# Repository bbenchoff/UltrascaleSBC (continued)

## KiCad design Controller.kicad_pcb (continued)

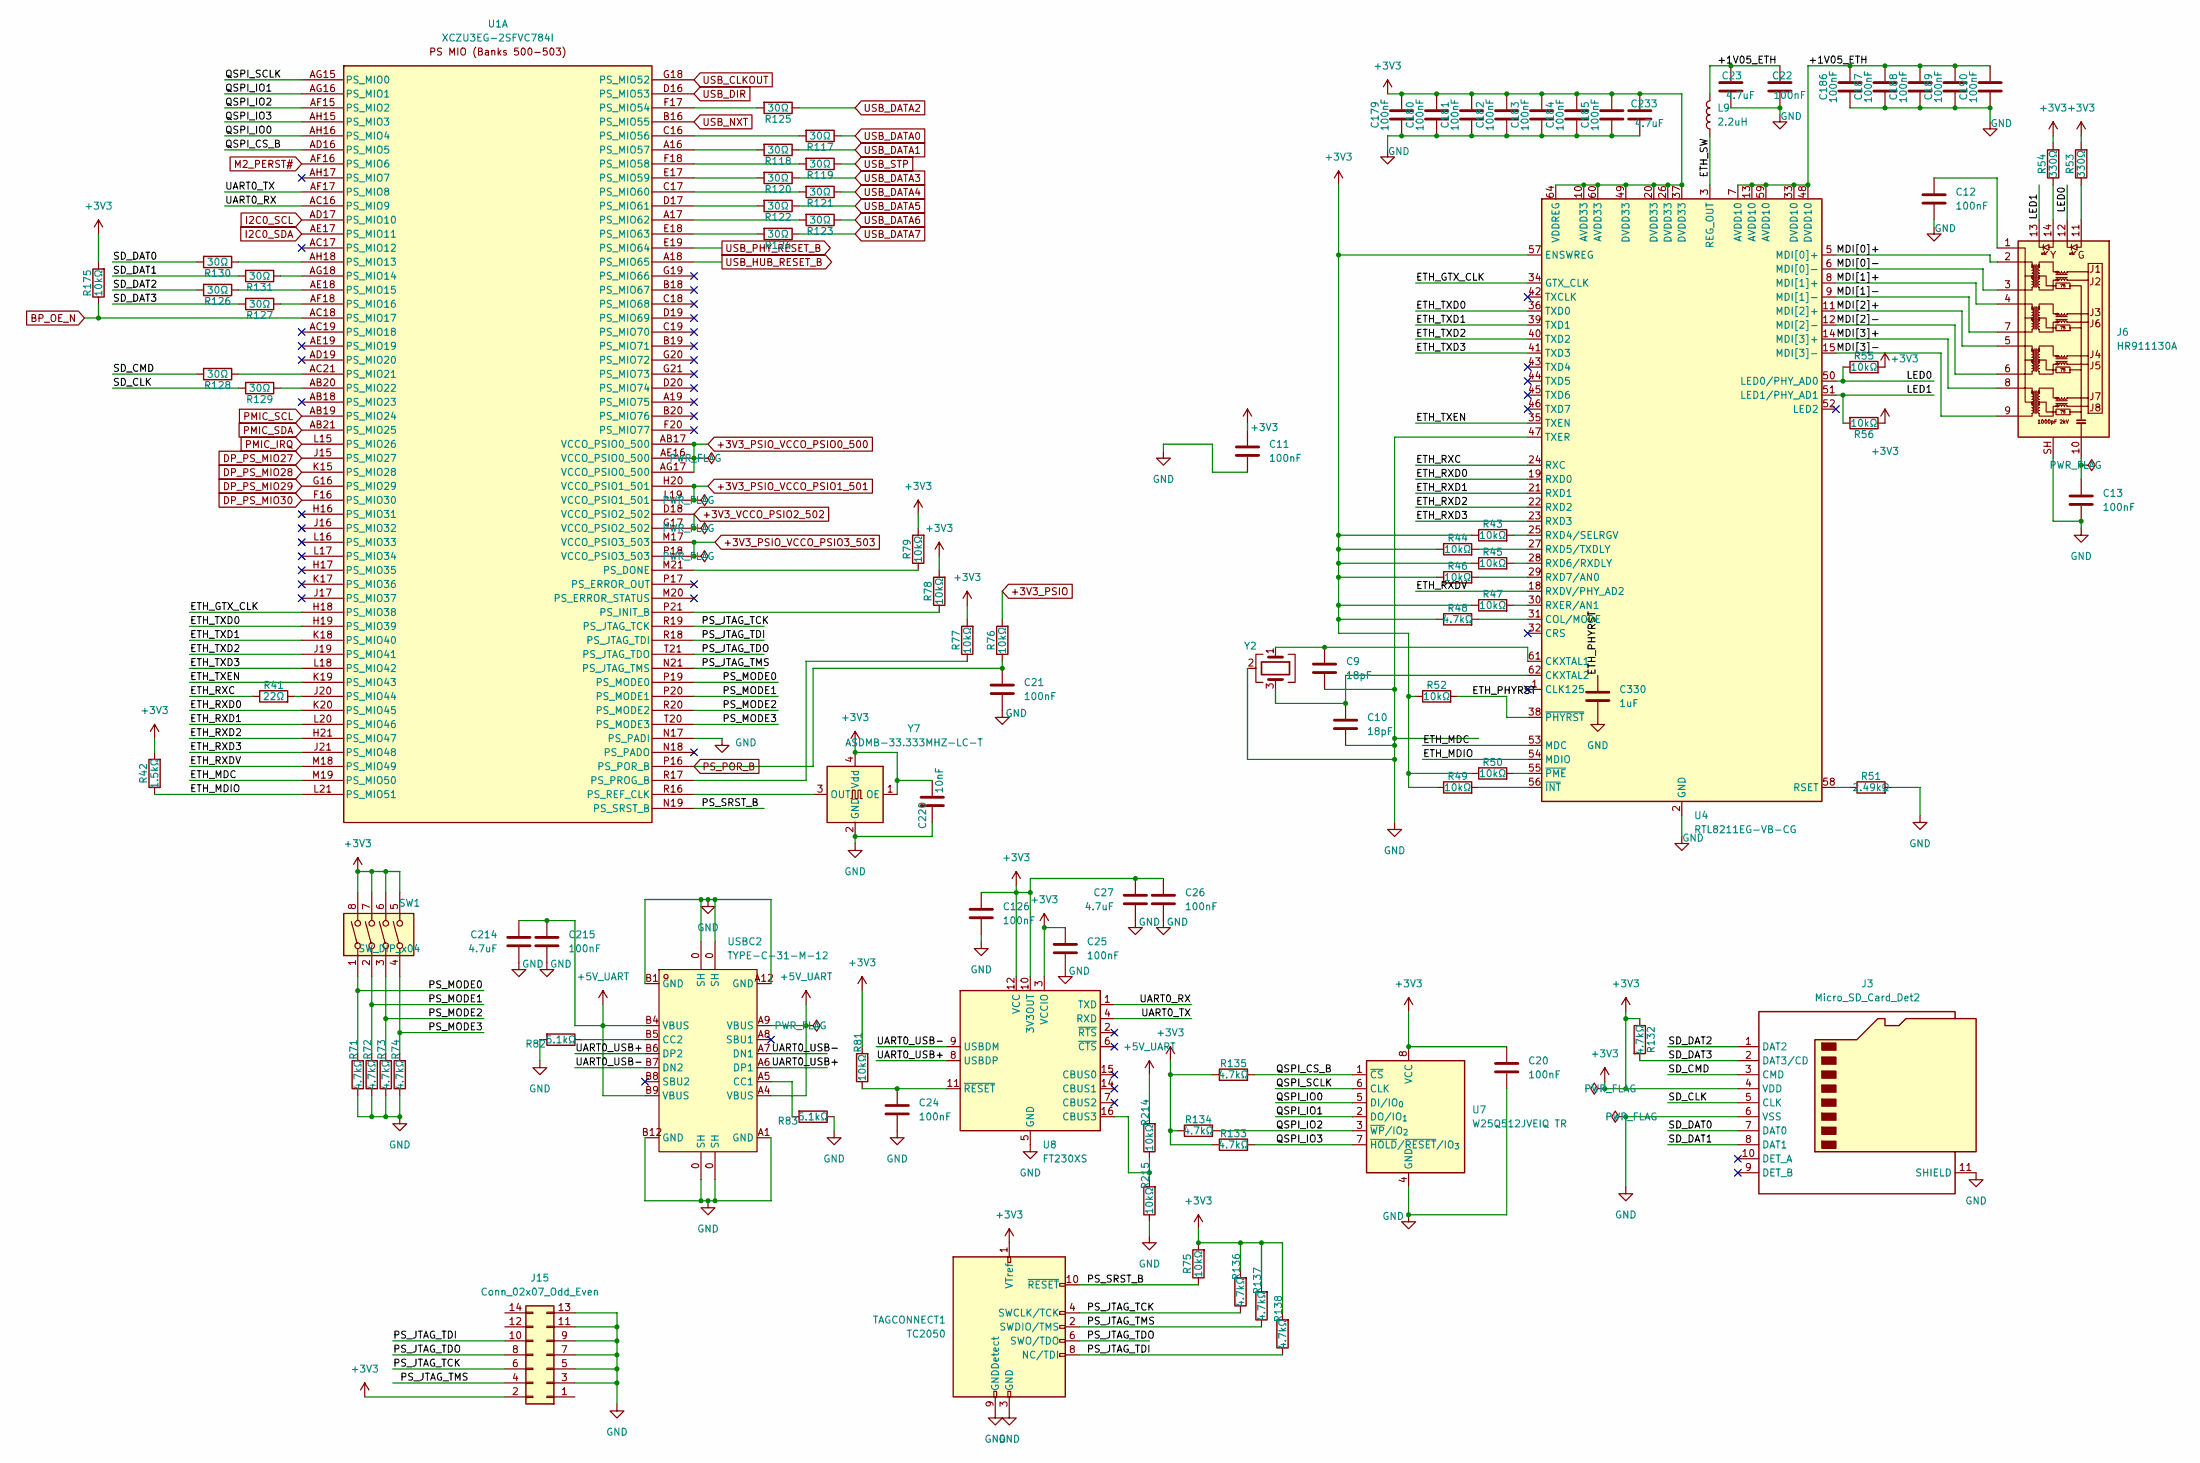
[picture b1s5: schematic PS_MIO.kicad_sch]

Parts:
C9, C10: 18pF; C_0402_1005Metric; MPN 0402CG180J500NT; LCSC C1549
C11, C179, C180, C181, C182, C183, C184, C185, C186, C187, C188, C189, C190: 100nF; C_0402_1005Metric; MPN CL05B104KO5NNNC; LCSC C1525
C12, C13, C20, C21, C22, C24, C25, C26, C126, C215: 100nF; C_1206_3216Metric; MPN CL31B104KBCNNNC; LCSC C24497
C23, C233: 4.7uF; C_0805_2012Metric; MPN CL21A475KPFNNNE; LCSC C96454
C27, C214: 4.7uF; C_1206_3216Metric; MPN 1206B475K500NT; LCSC C29823
C220: 10nF; C_0402_1005Metric; MPN CL05B103KB5NNNC; LCSC C15195
C330: 1uF; C_0402_1005Metric; MPN CL05A105KA5NQNC; LCSC C52923
J3: Micro_SD_Card_Det2; microSD_HC_Hirose_DM3AT-SF-PEJM5; MPN DM3AT-SF-PEJM5; LCSC C114218
J6: HR911130A; RJ45_Hanrun_HR911130A; MPN HR911130A; LCSC C54408
J15: Conn_02x07_Odd_Even; PinHeader_2x07_P2.00mm_Vertical; MPN 878311420; LCSC C240854
L9: 2.2uH; L_Bourns-SRN4018; MPN SRN4018-2R2M; LCSC C913207
R41: 22Ω; R_0402_1005Metric; Tolerance 1%; MPN 0402WGF220JTCE; LCSC C25092
R42: 1.5kΩ; R_0402_1005Metric; Tolerance 1%; MPN 0402WGF1501TCE; LCSC C25867
R43, R44, R45, R46, R47, R49, R50, R52, R55, R56, R75, R76, R77, R78, R79, R81, R175, R214, R215: 10kΩ; R_0402_1005Metric; Tolerance 1%; MPN 0402WGF1002TCE; LCSC C25744
R48, R71, R72, R73, R74, R132, R133, R134, R135, R136, R137, R138: 4.7kΩ; R_0402_1005Metric; Tolerance 1%; MPN 0402WGF4701TCE; LCSC C25900
R51: 2.49kΩ; R_0402_1005Metric; Tolerance 1%; MPN 0402WGF2491TCE; LCSC C25884
R53, R54: 330Ω; R_0402_1005Metric; Tolerance 1%; MPN 0402WGF3300TCE; LCSC C25104
R82, R83: 5.1kΩ; R_0402_1005Metric; Tolerance 1%; MPN 0402WGF5101TCE; LCSC C25905
R117, R118, R119, R120, R121, R122, R123, R124, R125, R126, R127, R128, R129, R130, R131: 30Ω; R_0402_1005Metric; Tolerance 1%; MPN RC0402FR-0730RL; LCSC C138007
SW1: SW_DIP_x04; SW_DIP_SPSTx04_Slide_6.7x11.72mm_W7.62mm_P2.54mm_LowProfile; MPN DSWB04LHGET; LCSC C99418
TAGCONNECT1: TC2050; Tag-Connect_TC2050-IDC-FP_2x05_P1.27mm_Vertical
U1: XCZU3EG-2SFVC784I; SFVC784_AMD; MPN XCZU3EG-2SFVC784I; LCSC C1550463
U4: RTL8211EG-VB-CG; QFN-64-1EP_9x9mm_P0.5mm_EP3.8x3.8mm; MPN RTL8211EG-VB-CG; LCSC C69264
U7: W25Q512JVEIQ TR; WSON-8-1EP_8x6mm_P1.27mm_EP3.4x4.3mm; MPN W25Q512JVEIQ; LCSC C7389628
U8: FT230XS; SSOP-16_3.9x4.9mm_P0.635mm; MPN FT230XS-R; LCSC C69082
USBC2: TYPE-C-31-M-12; USB-C_SMD-TYPE-C-31-M-12; MPN TYPE-C-31-M-12; LCSC Part C165948
Y2: Crystal_GND24; Crystal_SMD_3225-4Pin_3.2x2.5mm; Part Number X322525MOB4SI; LCSC C20617567
Y7: ASDMB-33.333MHZ-LC-T; ASDMB_2520; MPN ASDMB-33.333MHZ-LC-T; LCSC C17497075

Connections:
+3V3: C11.1, C20.1, C25.1, C26.1, C27.1, C126.1, C179.2, C180.2, C181.2, C182.2, C183.2, C184.2, C185.2, C220.2, C233.1, J3.4 (VDD), J15.2, R42.2, R43.1, R44.1, R45.1, R46.1, R47.1, R48.1, R49.1, R50.1, R52.1, R53.2, R54.2, R55.2, R56.1, R75.2, R77.2, R78.2, R79.2, R81.2, R132.1, R133.1, R134.1, R135.1, R136.2, R137.2, R138.2, R175.2, SW1.5, SW1.6, SW1.7, SW1.8, TAGCONNECT1.1 (VTref), U4.10 (AVDD33), U4.20 (DVDD33), U4.26 (DVDD33), U4.37 (DVDD33), U4.49 (DVDD33), U4.57 (ENSWREG), U4.60 (AVDD33), U4.64 (VDDREG), U7.8 (VCC), U8.3 (VCCIO), U8.10 (3V3OUT), U8.12 (VCC), Y7.1 (OE), Y7.4 (Vdd); also elsewhere on the board
+3V3_PSIO: R76.2, U1.AB17 (VCCO_PSIO0_500), U1.AE16 (VCCO_PSIO0_500), U1.AG17 (VCCO_PSIO0_500), U1.D18 (VCCO_PSIO2_502), U1.G17 (VCCO_PSIO2_502), U1.H20 (VCCO_PSIO1_501), U1.L19 (VCCO_PSIO1_501), U1.M17 (VCCO_PSIO3_503), U1.P18 (VCCO_PSIO3_503); also elsewhere on the board
+5V_UART: C214.1, C215.1, R214.2, USBC2.A4 (VBUS), USBC2.A9 (VBUS), USBC2.B4 (VBUS), USBC2.B9 (VBUS)
/PS_MIO/+1V05_ETH: C22.1, C23.1, C186.2, C187.2, C188.2, C189.2, C190.2, L9.2, U4.7 (AVDD10), U4.13 (AVDD10), U4.33 (DVDD10), U4.48 (DVDD10), U4.59 (AVDD10)
/PS_MIO/ETH_GTX_CLK: U1.H18 (PS_MIO38), U4.34 (GTX_CLK)
/PS_MIO/ETH_MDC: U1.M19 (PS_MIO50), U4.53 (MDC)
/PS_MIO/ETH_MDIO: R42.1, U1.L21 (PS_MIO51), U4.54 (MDIO)
/PS_MIO/ETH_PHYRST: C330.1, R52.2, U4.38 (~PHYRST)
/PS_MIO/ETH_RXC: R41.1, U4.24 (RXC)
/PS_MIO/ETH_RXD0: U1.K20 (PS_MIO45), U4.19 (RXD0)
/PS_MIO/ETH_RXD1: U1.L20 (PS_MIO46), U4.21 (RXD1)
/PS_MIO/ETH_RXD2: U1.H21 (PS_MIO47), U4.22 (RXD2)
/PS_MIO/ETH_RXD3: U1.J21 (PS_MIO48), U4.23 (RXD3)
/PS_MIO/ETH_RXDV: U1.M18 (PS_MIO49), U4.18 (RXDV/PHY_AD2)
/PS_MIO/ETH_SW: L9.1, U4.3 (REG_OUT)
/PS_MIO/ETH_TXD0: U1.H19 (PS_MIO39), U4.36 (TXD0)
/PS_MIO/ETH_TXD1: U1.K18 (PS_MIO40), U4.39 (TXD1)
/PS_MIO/ETH_TXD2: U1.J19 (PS_MIO41), U4.40 (TXD2)
/PS_MIO/ETH_TXD3: U1.L18 (PS_MIO42), U4.41 (TXD3)
/PS_MIO/ETH_TXEN: U1.K19 (PS_MIO43), U4.35 (TXEN)
/PS_MIO/LED0: J6.12, R55.1, U4.50 (LED0/PHY_AD0)
/PS_MIO/LED1: J6.13, R56.2, U4.51 (LED1/PHY_AD1)
/PS_MIO/MDI[0]+: J6.2 (TD1+), U4.5 (MDI[0]+)
/PS_MIO/MDI[0]-: J6.3 (TD1-), U4.6 (MDI[0]-)
/PS_MIO/MDI[1]+: J6.4 (TD2+), U4.8 (MDI[1]+)
/PS_MIO/MDI[1]-: J6.7 (TD2-), U4.9 (MDI[1]-)
/PS_MIO/MDI[2]+: J6.5 (TD3+), U4.11 (MDI[2]+)
/PS_MIO/MDI[2]-: J6.6 (TD3-), U4.12 (MDI[2]-)
/PS_MIO/MDI[3]+: J6.8 (TD4+), U4.14 (MDI[3]+)
/PS_MIO/MDI[3]-: J6.9 (TD4-), U4.15 (MDI[3]-)
/PS_MIO/PS_JTAG_TCK: J15.6, R136.1, TAGCONNECT1.4 (SWCLK/TCK), U1.R19 (PS_JTAG_TCK)
/PS_MIO/PS_JTAG_TDI: J15.10, R138.1, TAGCONNECT1.8 (NC/TDI), U1.R18 (PS_JTAG_TDI)
/PS_MIO/PS_JTAG_TDO: J15.8, TAGCONNECT1.6 (SWO/TDO), U1.T21 (PS_JTAG_TDO)
/PS_MIO/PS_JTAG_TMS: J15.4, R137.1, TAGCONNECT1.2 (SWDIO/TMS), U1.N21 (PS_JTAG_TMS)
/PS_MIO/PS_MODE0: R71.2, SW1.1, U1.P19 (PS_MODE0)
/PS_MIO/PS_MODE1: R72.2, SW1.2, U1.P20 (PS_MODE1)
/PS_MIO/PS_MODE2: R73.2, SW1.3, U1.R20 (PS_MODE2)
/PS_MIO/PS_MODE3: R74.2, SW1.4, U1.T20 (PS_MODE3)
/PS_MIO/PS_SRST_B: R75.1, TAGCONNECT1.10 (~RESET), U1.N19 (PS_SRST_B); also elsewhere on the board
/PS_MIO/QSPI_CS_B: R135.2, U1.AD16 (PS_MIO5), U7.1 (~CS)
/PS_MIO/QSPI_IO0: U1.AH16 (PS_MIO4), U7.5 (DI/IO_{0})
/PS_MIO/QSPI_IO1: U1.AG16 (PS_MIO1), U7.2 (DO/IO_{1})
/PS_MIO/QSPI_IO2: R134.2, U1.AF15 (PS_MIO2), U7.3 (~WP/IO_{2})
/PS_MIO/QSPI_IO3: R133.2, U1.AH15 (PS_MIO3), U7.7 (~HOLD/~RESET/IO_{3})
/PS_MIO/QSPI_SCLK: U1.AG15 (PS_MIO0), U7.6 (CLK)
/PS_MIO/SD_CLK: J3.5 (CLK), R129.2
/PS_MIO/SD_CMD: J3.3 (CMD), R128.2
/PS_MIO/SD_DAT0: J3.7 (DAT0), R130.2
/PS_MIO/SD_DAT1: J3.8 (DAT1), R131.2
/PS_MIO/SD_DAT2: J3.1 (DAT2), R126.2
/PS_MIO/SD_DAT3: J3.2 (DAT3/CD), R127.2, R132.2
/PS_MIO/UART0_RX: U1.AC16 (PS_MIO9), U8.1 (TXD)
/PS_MIO/UART0_TX: U1.AF17 (PS_MIO8), U8.4 (RXD)
/PS_MIO/UART0_USB+: U8.8 (USBDP), USBC2.A6 (DP1), USBC2.B6 (DP2)
/PS_MIO/UART0_USB-: U8.9 (USBDM), USBC2.A7 (DN1), USBC2.B7 (DN2)
BP_OE_N: R175.1, U1.AC18 (PS_MIO17); also elsewhere on the board
DP_HPD: U1.K15 (PS_MIO28); also elsewhere on the board
DP_PS_MIO27: U1.J15 (PS_MIO27); also elsewhere on the board
DP_PS_MIO29: U1.G16 (PS_MIO29); also elsewhere on the board
DP_PS_MIO30: U1.F16 (PS_MIO30); also elsewhere on the board
GND: C9.2, C10.2, C11.2, C12.2, C13.2, C20.2, C21.2, C22.2, C23.2, C24.2, C25.2, C26.2, C27.2, C126.2, C179.1, C180.1, C181.1, C182.1, C183.1, C184.1, C185.1, C186.1, C187.1, C188.1, C189.1, C190.1, C214.2, C215.2, C220.1, C233.2, C330.2, J3.6 (VSS), J3.11 (SHIELD), J6.SH, J15.3, J15.5, J15.7, J15.9, J15.11, J15.13, R51.2, R71.1, R72.1, R73.1, R74.1, R82.2, R83.1, R215.1, TAGCONNECT1.3 (GND), TAGCONNECT1.5 (GND), TAGCONNECT1.9 (GNDDetect), U1.N17 (PS_PADI), U4.2 (GND), U4.4 (GND), U4.47 (TXER), U4.63 (GND), U4.65 (GND), U7.4 (GND), U8.5 (GND), U8.13 (GND), USBC2.0 (SH), USBC2.A1 (GND), USBC2.A12 (GND), USBC2.B1 (GND), USBC2.B12 (GND), Y2.2 (G), Y2.4 (G), Y7.2 (GND); also elsewhere on the board
I2C0_SCL: U1.AD17 (PS_MIO10); also elsewhere on the board
I2C0_SDA: U1.AE17 (PS_MIO11); also elsewhere on the board
M2_PERST#: U1.AF16 (PS_MIO6); also elsewhere on the board
unnamed: C12.1, J6.1 (CT)
unnamed: C13.1, J6.10 (GND)
unnamed: J6.11, R53.1
unnamed: J6.14, R54.1
unnamed: R79.1, U1.M21 (PS_DONE)
unnamed: R78.1, U1.P21 (PS_INIT_B)
unnamed: R130.1, U1.AH18 (PS_MIO13)
unnamed: R131.1, U1.AG18 (PS_MIO14)
unnamed: R126.1, U1.AE18 (PS_MIO15)
unnamed: R127.1, U1.AF18 (PS_MIO16)
unnamed: R128.1, U1.AC21 (PS_MIO21)
unnamed: R129.1, U1.AB20 (PS_MIO22)
unnamed: R41.2, U1.J20 (PS_MIO44)
unnamed: R125.2, U1.F17 (PS_MIO54)
unnamed: R117.2, U1.C16 (PS_MIO56)
unnamed: R118.2, U1.A16 (PS_MIO57)
unnamed: R119.2, U1.F18 (PS_MIO58)
unnamed: R120.2, U1.E17 (PS_MIO59)
unnamed: R121.2, U1.C17 (PS_MIO60)
unnamed: R122.2, U1.D17 (PS_MIO61)
unnamed: R123.2, U1.A17 (PS_MIO62)
unnamed: R124.2, U1.E18 (PS_MIO63)
unnamed: R77.1, U1.R17 (PS_PROG_B)
unnamed: U1.R16 (PS_REF_CLK), Y7.3 (OUT)
unnamed: C9.1, U4.61 (CKXTAL1), Y2.1
unnamed: C10.1, U4.62 (CKXTAL2), Y2.3
unnamed: R48.2, U4.31 (COL/MODE)
unnamed: R51.1, U4.58 (RSET)
unnamed: R43.2, U4.25 (RXD4/SELRGV)
unnamed: R44.2, U4.27 (RXD5/TXDLY)
unnamed: R45.2, U4.28 (RXD6/RXDLY)
unnamed: R46.2, U4.29 (RXD7/AN0)
unnamed: R47.2, U4.30 (RXER/AN1)
unnamed: R49.2, U4.56 (~INT)
unnamed: R50.2, U4.55 (~PME)
unnamed: R214.1, R215.2, U8.16 (CBUS3)
unnamed: C24.1, R81.1, U8.11 (~RESET)
unnamed: R83.2, USBC2.A5 (CC1)
unnamed: R82.1, USBC2.B5 (CC2)
PMIC_IRQ: U1.L15 (PS_MIO26); also elsewhere on the board
PMIC_SCL: U1.AB19 (PS_MIO24); also elsewhere on the board
PMIC_SDA: U1.AB21 (PS_MIO25); also elsewhere on the board
PS_POR_B: C21.1, R76.1, U1.P16 (PS_POR_B); also elsewhere on the board
USB_CLKOUT: U1.G18 (PS_MIO52); also elsewhere on the board
USB_DATA0: R117.1; also elsewhere on the board
USB_DATA1: R118.1; also elsewhere on the board
USB_DATA2: R125.1; also elsewhere on the board
USB_DATA3: R120.1; also elsewhere on the board
USB_DATA4: R121.1; also elsewhere on the board
USB_DATA5: R122.1; also elsewhere on the board
USB_DATA6: R123.1; also elsewhere on the board
USB_DATA7: R124.1; also elsewhere on the board
USB_DIR: U1.D16 (PS_MIO53); also elsewhere on the board
USB_HUB_RESET_B: U1.A18 (PS_MIO65); also elsewhere on the board
USB_NXT: U1.B16 (PS_MIO55); also elsewhere on the board
USB_PHY_RESET_B: U1.E19 (PS_MIO64); also elsewhere on the board
USB_STP: R119.1; also elsewhere on the board

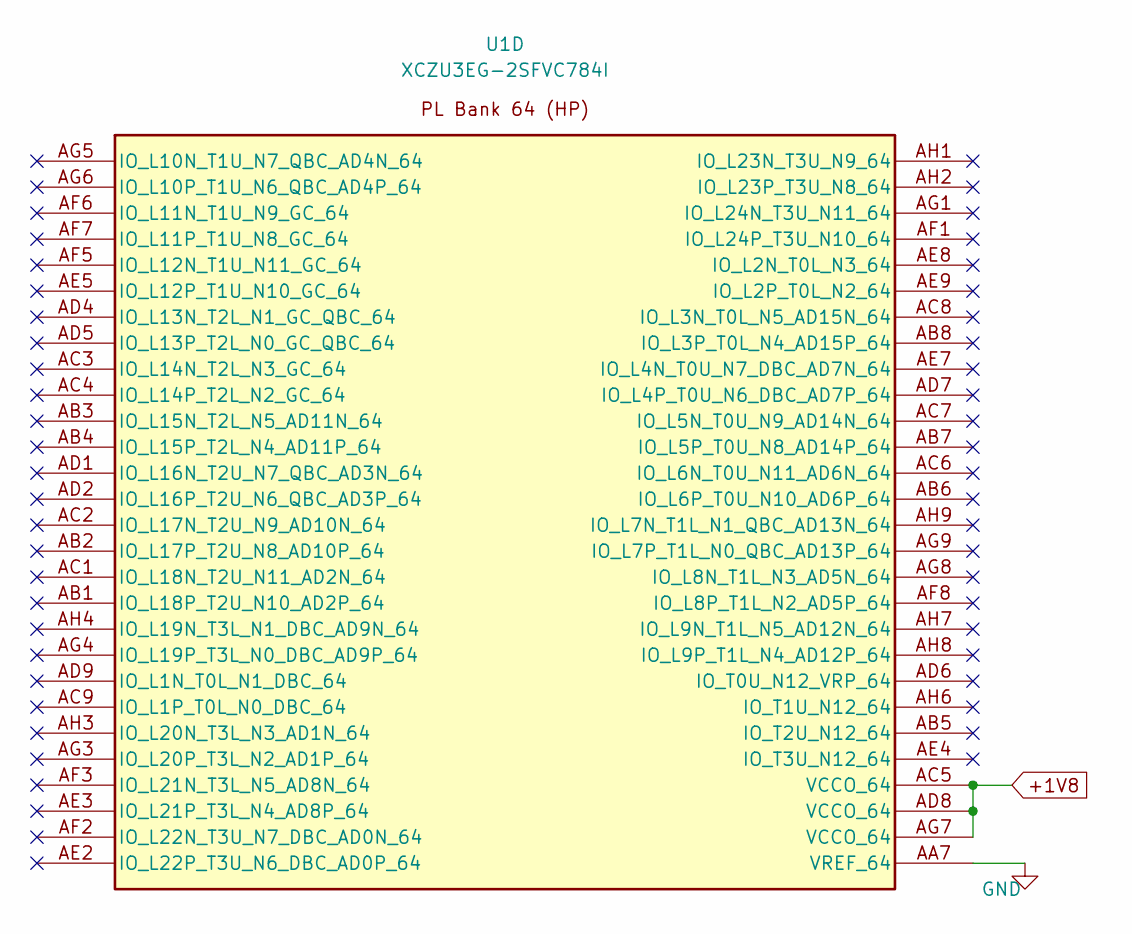
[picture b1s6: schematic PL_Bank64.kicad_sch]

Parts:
U1: XCZU3EG-2SFVC784I; SFVC784_AMD; MPN XCZU3EG-2SFVC784I; LCSC C1550463

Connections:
+1V8: U1.AC5 (VCCO_64), U1.AD8 (VCCO_64), U1.AG7 (VCCO_64); also elsewhere on the board
GND: U1.AA7 (VREF_64); also elsewhere on the board

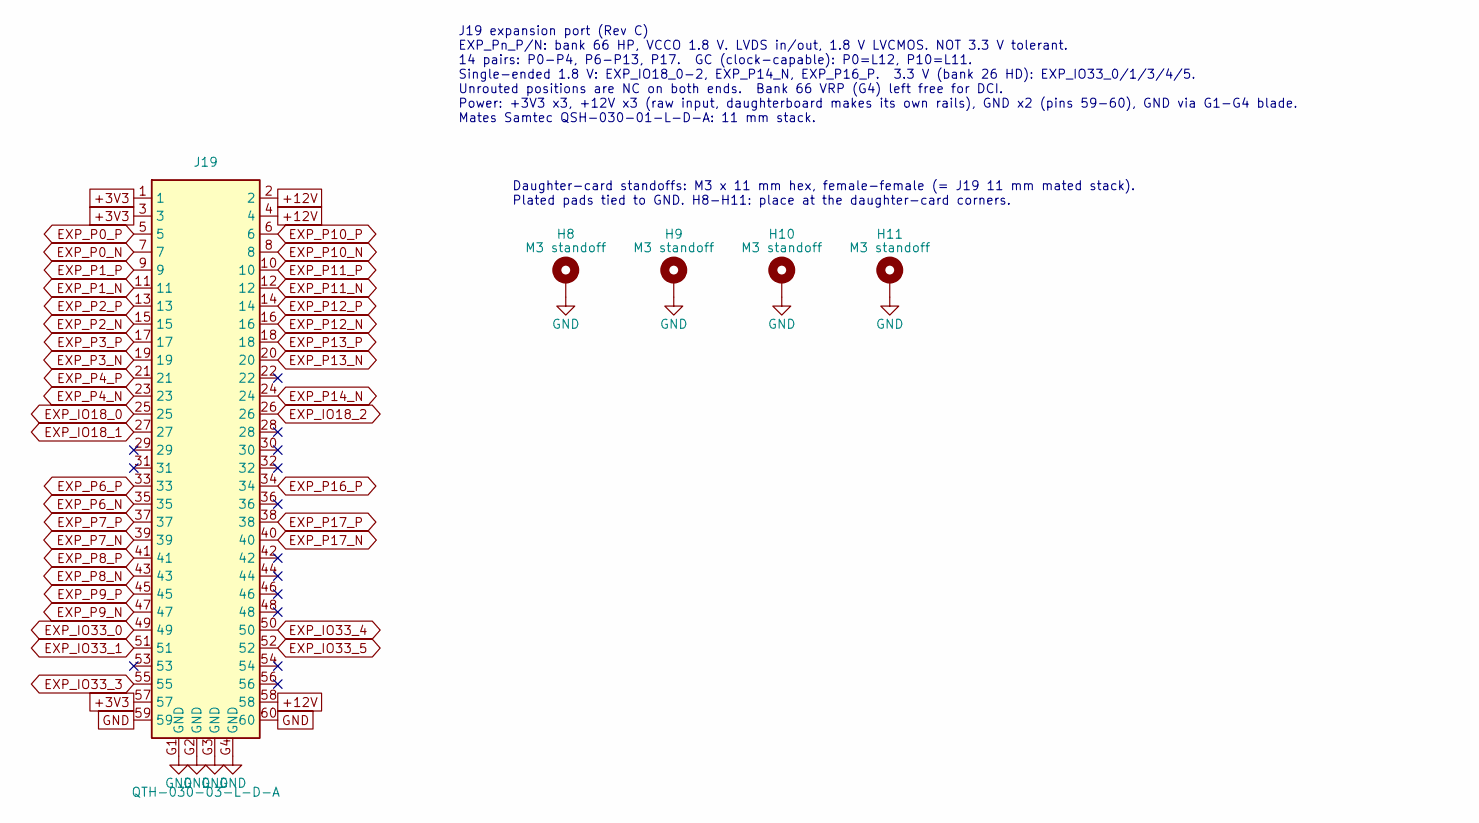
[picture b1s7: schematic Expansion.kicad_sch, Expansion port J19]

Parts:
H8, H9, H10, H11: M3 standoff; MountingHole_3.2mm_M3_Pad_Via
J19: QTH-030-03-L-D-A; Samtec_QTH-030-03-L-D-A; MPN QTH-030-03-L-D-A; LCSC C5296114

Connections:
+3V3: J19.1, J19.3, J19.57; also elsewhere on the board
+12V: J19.2, J19.4, J19.58; also elsewhere on the board
EXP_IO18_0: J19.25; also elsewhere on the board
EXP_IO18_1: J19.27; also elsewhere on the board
EXP_IO18_2: J19.26; also elsewhere on the board
EXP_IO33_0: J19.49; also elsewhere on the board
EXP_IO33_1: J19.51; also elsewhere on the board
EXP_IO33_3: J19.55; also elsewhere on the board
EXP_IO33_4: J19.50; also elsewhere on the board
EXP_IO33_5: J19.52; also elsewhere on the board
EXP_P0_N: J19.7; also elsewhere on the board
EXP_P0_P: J19.5; also elsewhere on the board
EXP_P1_N: J19.11; also elsewhere on the board
EXP_P1_P: J19.9; also elsewhere on the board
EXP_P2_N: J19.15; also elsewhere on the board
EXP_P2_P: J19.13; also elsewhere on the board
EXP_P3_N: J19.19; also elsewhere on the board
EXP_P3_P: J19.17; also elsewhere on the board
EXP_P4_N: J19.23; also elsewhere on the board
EXP_P4_P: J19.21; also elsewhere on the board
EXP_P6_N: J19.35; also elsewhere on the board
EXP_P6_P: J19.33; also elsewhere on the board
EXP_P7_N: J19.39; also elsewhere on the board
EXP_P7_P: J19.37; also elsewhere on the board
EXP_P8_N: J19.43; also elsewhere on the board
EXP_P8_P: J19.41; also elsewhere on the board
EXP_P9_N: J19.47; also elsewhere on the board
EXP_P9_P: J19.45; also elsewhere on the board
EXP_P10_N: J19.8; also elsewhere on the board
EXP_P10_P: J19.6; also elsewhere on the board
EXP_P11_N: J19.12; also elsewhere on the board
EXP_P11_P: J19.10; also elsewhere on the board
EXP_P12_N: J19.16; also elsewhere on the board
EXP_P12_P: J19.14; also elsewhere on the board
EXP_P13_N: J19.20; also elsewhere on the board
EXP_P13_P: J19.18; also elsewhere on the board
EXP_P14_N: J19.24; also elsewhere on the board
EXP_P16_P: J19.34; also elsewhere on the board
EXP_P17_N: J19.40; also elsewhere on the board
EXP_P17_P: J19.38; also elsewhere on the board
GND: H8.1 (1_1), H9.1 (1_1), H10.1 (1_1), H11.1 (1_1), J19.59, J19.60, J19.G1 (GND), J19.G2 (GND), J19.G3 (GND), J19.G4 (GND); also elsewhere on the board

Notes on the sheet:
J19 expansion port (Rev C) EXP_Pn_P/N: bank 66 HP, VCCO 1.8 V. LVDS in/out, 1.8 V LVCMOS. NOT 3.3 V tolerant. 14 pairs: P0-P4, P6-P13, P17. GC (clock-capable): P0=L12, P10=L11. Single-ended 1.8 V: EXP_IO18_0-2, EXP_P14_N, EXP_P16_P. 3.3 V (bank 26 HD): EXP_IO33_0/1/3/4/5. Unrouted positions are NC 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
Daughter-card standoffs: M3 x 11 mm hex, female-female (= J19 11 mm mated stack). Plated pads tied to GND. H8-H11: place at the daughter-card corners.

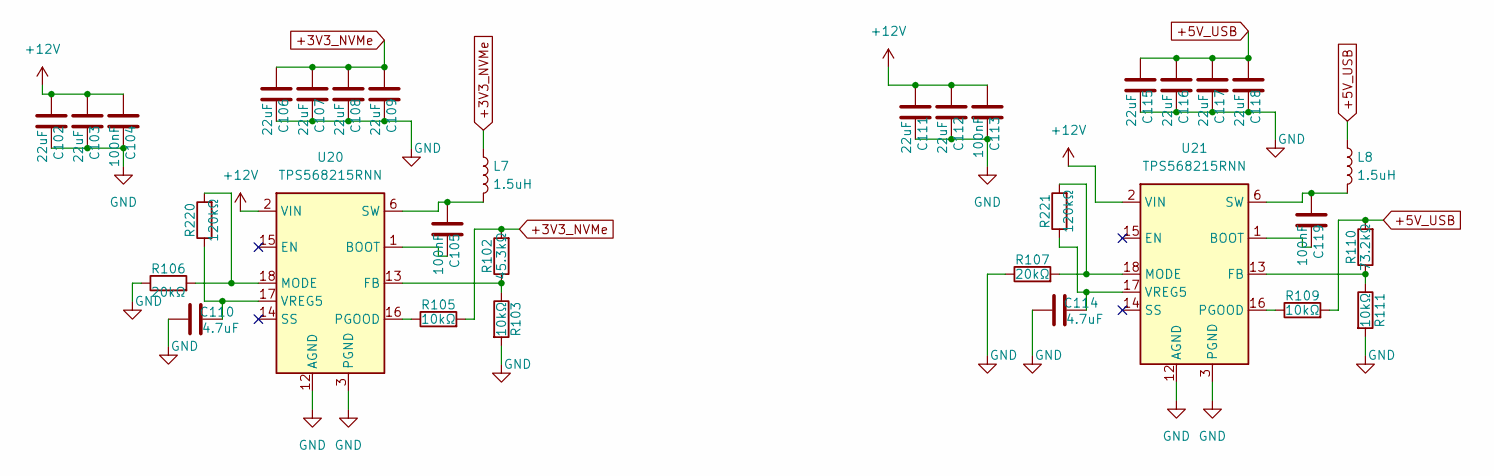
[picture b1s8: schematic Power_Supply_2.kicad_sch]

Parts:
C102, C103, C111, C112: 22uF; C_0805_2012Metric; MPN CGA0805X5R226M250MT; LCSC C6119899
C104, C105, C113, C119: 100nF; C_0402_1005Metric; MPN CL05B104KO5NNNC; LCSC C1525
C106, C107, C108, C109, C115, C116, C117, C118: 22uF; C_0603_1608Metric; MPN CC0603MRX5R5BB226; LCSC C109448
C110, C114: 4.7uF; C_0805_2012Metric; MPN CL21A475KAQNNNE; LCSC C1779
L7, L8: 1.5uH; L_Bourns_SRP6060FA; MPN FEXL0630A-1R5M; LCSC C5378526
R102: 45.3kΩ; R_0402_1005Metric; Tolerance 1%; MPN WR04X4532FTL; LCSC C170321
R103, R105, R109, R111: 10kΩ; R_0402_1005Metric; Tolerance 1%; MPN 0402WGF1002TCE; LCSC C25744
R106, R107: 20kΩ; R_0402_1005Metric; Tolerance 1%; MPN 0402WGF2002TCE; LCSC C25765
R110: 73.2kΩ; R_0402_1005Metric; Tolerance 1%; MPN FRC0402F7322TS; LCSC C2998163
R220, R221: 120kΩ; R_0402_1005Metric; Tolerance 1%; MPN 0402WGF1203TCE; LCSC C25750
U20, U21: TPS568215RNN; Texas_RNN0018A; MPN TPS568215RNNR; LCSC C473367

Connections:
+3V3_NVMe: C106.1, C107.1, C108.1, C109.1, L7.1, R102.2, R105.2; also elsewhere on the board
+5V_USB: C115.1, C116.1, C117.1, C118.1, L8.1, R109.2, R110.2; also elsewhere on the board
+12V: C102.1, C103.1, C104.1, C111.1, C112.1, C113.1, U20.2 (VIN), U20.11 (VIN), U21.2 (VIN), U21.11 (VIN); also elsewhere on the board
GND: C102.2, C103.2, C104.2, C106.2, C107.2, C108.2, C109.2, C110.1, C111.2, C112.2, C113.2, C114.1, C115.2, C116.2, C117.2, C118.2, R103.2, R106.1, R107.1, R111.2, U20.3 (PGND), U20.4 (PGND), U20.5 (PGND), U20.8 (PGND), U20.9 (PGND), U20.10 (PGND), U20.12 (AGND), U21.3 (PGND), U21.4 (PGND), U21.5 (PGND), U21.8 (PGND), U21.9 (PGND), U21.10 (PGND), U21.12 (AGND); also elsewhere on the board
unnamed: C105.1, L7.2, U20.6 (SW), U20.7 (SW)
unnamed: C119.1, L8.2, U21.6 (SW), U21.7 (SW)
unnamed: C105.2, U20.1 (BOOT)
unnamed: R102.1, R103.1, U20.13 (FB)
unnamed: R106.2, R220.2, U20.18 (MODE)
unnamed: R105.1, U20.16 (PGOOD)
unnamed: C110.2, R220.1, U20.17 (VREG5)
unnamed: C119.2, U21.1 (BOOT)
unnamed: R110.1, R111.1, U21.13 (FB)
unnamed: R107.2, R221.2, U21.18 (MODE)
unnamed: R109.1, U21.16 (PGOOD)
unnamed: C114.2, R221.1, U21.17 (VREG5)

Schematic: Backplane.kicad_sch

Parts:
C197, C198, C199, C200, C201: 10uF; C_0402_1005Metric; MPN CL05A106MP5NUNC; LCSC C315248
C202, C203, C204, C205, C206: 100nF; C_0402_1005Metric; MPN CL05B104KO5NNNC; LCSC C1525
J13: 09185606324; Mouser Part Number 617-09185606324
U14, U15, U28, U29, U30, U31, U32, U33, U34, U35: SRV05-4; SOT-23-6; MPN SRV05-4; LCSC C7420376
U16, U17, U18, U19, U27: 74LVC244; SSOP-20_4.4x6.5mm_P0.65mm; Part 74LVC244APW,118; LCSC C6079

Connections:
+3V3: C197.1, C198.1, C199.1, C200.1, C201.1, C202.1, C203.1, C204.1, C205.1, C206.1, J13.60, U14.5 (VP), U15.5 (VP), U16.20 (VCC), U17.20 (VCC), U18.20 (VCC), U19.20 (VCC), U27.20 (VCC), U28.5 (VP), U29.5 (VP), U30.5 (VP), U31.5 (VP), U32.5 (VP), U33.5 (VP), U34.5 (VP), U35.5 (VP); also elsewhere on the board
/Backplane/I2C_SCL: J13.11, U15.6 (IO4), U18.12 (1Y3)
/Backplane/RX0: J13.14, U27.2 (1A0), U28.6 (IO4)
/Backplane/RX1: J13.16, U27.4 (1A1), U28.4 (IO3)
/Backplane/RX2: J13.20, U27.6 (1A2), U29.6 (IO4)
/Backplane/RX3: J13.22, U27.8 (1A3), U29.4 (IO3)
/Backplane/RX4: J13.34, U27.11 (2A3), U31.4 (IO3)
/Backplane/RX5: J13.32, U27.13 (2A2), U31.6 (IO4)
/Backplane/RX6: J13.28, U27.15 (2A1), U30.4 (IO3)
/Backplane/RX7: J13.26, U27.17 (2A0), U30.6 (IO4)
/Backplane/RX8: J13.38, U19.2 (1A0), U32.6 (IO4)
/Backplane/RX9: J13.40, U19.4 (1A1), U32.4 (IO3)
/Backplane/RX10: J13.44, U19.6 (1A2), U33.6 (IO4)
/Backplane/RX11: J13.46, U19.8 (1A3), U33.4 (IO3)
/Backplane/RX12: J13.58, U19.11 (2A3), U35.4 (IO3)
/Backplane/RX13: J13.56, U19.13 (2A2), U35.6 (IO4)
/Backplane/RX14: J13.52, U19.15 (2A1), U34.4 (IO3)
/Backplane/RX15: J13.50, U19.17 (2A0), U34.6 (IO4)
/Backplane/SPI_CS: J13.3, U14.3 (IO2), U18.13 (2A2)
/Backplane/SPI_MISO: J13.2, U14.6 (IO4), U18.18 (1Y0)
/Backplane/SPI_MOSI: J13.1, U14.1 (IO1), U18.15 (2A1)
/Backplane/SPI_SCK: J13.4, U14.4 (IO3), U18.11 (2A3)
/Backplane/TDMA_CLK: J13.7, U15.1 (IO1), U18.16 (1Y1)
/Backplane/TDMA_SYNC: J13.9, U15.3 (IO2), U18.14 (1Y2)
/Backplane/TX0: J13.13, U16.18 (1Y0), U28.1 (IO1)
/Backplane/TX1: J13.15, U16.16 (1Y1), U28.3 (IO2)
/Backplane/TX2: J13.19, U16.14 (1Y2), U29.1 (IO1)
/Backplane/TX3: J13.21, U16.12 (1Y3), U29.3 (IO2)
/Backplane/TX4: J13.33, U16.9 (2Y3), U31.3 (IO2)
/Backplane/TX5: J13.31, U16.7 (2Y2), U31.1 (IO1)
/Backplane/TX6: J13.27, U16.5 (2Y1), U30.3 (IO2)
/Backplane/TX7: J13.25, U16.3 (2Y0), U30.1 (IO1)
/Backplane/TX8: J13.37, U17.18 (1Y0), U32.1 (IO1)
/Backplane/TX9: J13.39, U17.16 (1Y1), U32.3 (IO2)
/Backplane/TX10: J13.43, U17.14 (1Y2), U33.1 (IO1)
/Backplane/TX11: J13.45, U17.12 (1Y3), U33.3 (IO2)
/Backplane/TX12: J13.57, U17.9 (2Y3), U35.3 (IO2)
/Backplane/TX13: J13.55, U17.7 (2Y2), U35.1 (IO1)
/Backplane/TX14: J13.51, U17.5 (2Y1), U34.3 (IO2)
/Backplane/TX15: J13.49, U17.3 (2Y0), U34.1 (IO1)
BP_I2C_SCL_BUF: U18.8 (1A3); also elsewhere on the board
BP_I2C_SDA: J13.12, U15.4 (IO3); also elsewhere on the board
BP_OE_N: U16.1 (1OE), U16.19 (2OE), U17.1 (1OE), U17.19 (2OE), U18.1 (1OE), U18.19 (2OE), U19.1 (1OE), U19.19 (2OE), U27.1 (1OE), U27.19 (2OE); also elsewhere on the board
GND: C197.2, C198.2, C199.2, C200.2, C201.2, C202.2, C203.2, C204.2, C205.2, C206.2, J13.5, J13.6, J13.8, J13.10, J13.17, J13.18, J13.23, J13.24, J13.29, J13.30, J13.35, J13.36, J13.41, J13.42, J13.47, J13.48, J13.53, J13.54, J13.59, U14.2 (VN), U15.2 (VN), U16.10 (GND), U17.10 (GND), U18.10 (GND), U18.17 (2A0), U19.10 (GND), U27.10 (GND), U28.2 (VN), U29.2 (VN), U30.2 (VN), U31.2 (VN), U32.2 (VN), U33.2 (VN), U34.2 (VN), U35.2 (VN); also elsewhere on the board
LED_SPI_CS_BUF: U18.7 (2Y2); also elsewhere on the board
LED_SPI_MISO_BUF: U18.2 (1A0); also elsewhere on the board
LED_SPI_MOSI_BUF: U18.5 (2Y1); also elsewhere on the board
LED_SPI_SCK_BUF: U18.9 (2Y3); also elsewhere on the board
TDMA_CLK_BUF: U18.4 (1A1); also elsewhere on the board
TDMA_SYNC_BUF: U18.6 (1A2); also elsewhere on the board
UART_RX_BUF_0: U27.18 (1Y0); also elsewhere on the board
UART_RX_BUF_1: U27.16 (1Y1); also elsewhere on the board
UART_RX_BUF_2: U27.14 (1Y2); also elsewhere on the board
UART_RX_BUF_3: U27.12 (1Y3); also elsewhere on the board
UART_RX_BUF_4: U27.9 (2Y3); also elsewhere on the board
UART_RX_BUF_5: U27.7 (2Y2); also elsewhere on the board
UART_RX_BUF_6: U27.5 (2Y1); also elsewhere on the board
UART_RX_BUF_7: U27.3 (2Y0); also elsewhere on the board
UART_RX_BUF_8: U19.18 (1Y0); also elsewhere on the board
UART_RX_BUF_9: U19.16 (1Y1); also elsewhere on the board
UART_RX_BUF_10: U19.14 (1Y2); also elsewhere on the board
UART_RX_BUF_11: U19.12 (1Y3); also elsewhere on the board
UART_RX_BUF_12: U19.9 (2Y3); also elsewhere on the board
UART_RX_BUF_13: U19.7 (2Y2); also elsewhere on the board
UART_RX_BUF_14: U19.5 (2Y1); also elsewhere on the board
UART_RX_BUF_15: U19.3 (2Y0); also elsewhere on the board
UART_TX_BUF_0: U16.2 (1A0); also elsewhere on the board
UART_TX_BUF_1: U16.4 (1A1); also elsewhere on the board
UART_TX_BUF_2: U16.6 (1A2); also elsewhere on the board
UART_TX_BUF_3: U16.8 (1A3); also elsewhere on the board
UART_TX_BUF_4: U16.11 (2A3); also elsewhere on the board
UART_TX_BUF_5: U16.13 (2A2); also elsewhere on the board
UART_TX_BUF_6: U16.15 (2A1); also elsewhere on the board
UART_TX_BUF_7: U16.17 (2A0); also elsewhere on the board
UART_TX_BUF_8: U17.2 (1A0); also elsewhere on the board
UART_TX_BUF_9: U17.4 (1A1); also elsewhere on the board
UART_TX_BUF_10: U17.6 (1A2); also elsewhere on the board
UART_TX_BUF_11: U17.8 (1A3); also elsewhere on the board
UART_TX_BUF_12: U17.11 (2A3); also elsewhere on the board
UART_TX_BUF_13: U17.13 (2A2); also elsewhere on the board
UART_TX_BUF_14: U17.15 (2A1); also elsewhere on the board
UART_TX_BUF_15: U17.17 (2A0); also elsewhere on the board

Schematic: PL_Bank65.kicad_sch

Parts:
U1: XCZU3EG-2SFVC784I; SFVC784_AMD; MPN XCZU3EG-2SFVC784I; LCSC C1550463

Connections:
+1V8: U1.H5 (VCCO_65), U1.J3 (VCCO_65), U1.L4 (VCCO_65); also elsewhere on the board
GND: U1.R9 (VREF_65); also elsewhere on the board

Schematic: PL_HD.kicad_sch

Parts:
R139, R140, R141, R142, R143, R144, R145, R146, R147, R148, R149, R150, R151, R152, R153, R154, R155, R156, R157, R158, R159, R160, R161, R162, R163, R164, R165, R166, R167, R168, R169, R170, R171, R172, R173, R174, R197: 22Ω; R_0402_1005Metric; Tolerance 1%; MPN 0402WGF220JTCE; LCSC C25092
R176, R177: 4.7kΩ; R_0402_1005Metric; Tolerance 1%; MPN 0402WGF4701TCE; LCSC C25900
R178, R179, R180, R181, R182, R183, R184, R185, R186, R187, R188, R189, R190, R191, R192, R193, R194, R195, R196: 10kΩ; R_0402_1005Metric; Tolerance 1%; MPN 0402WGF1002TCE; LCSC C25744
U1: XCZU3EG-2SFVC784I; SFVC784_AMD; MPN XCZU3EG-2SFVC784I; LCSC C1550463

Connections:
+3V3: R176.1, R177.1, R178.1, R179.1, R180.1, R181.1, R182.1, R183.1, R184.1, R185.1, R186.1, R187.1, R188.1, R189.1, R190.1, R191.1, R192.1, R193.1, R194.1, R195.1, R196.1, U1.AA14 (VCCO_24), U1.AC10 (VCCO_44), U1.AD13 (VCCO_24), U1.AG12 (VCCO_44), U1.B12 (VCCO_25), U1.C15 (VCCO_26), U1.E11 (VCCO_25), U1.F14 (VCCO_26); also elsewhere on the board
BP_I2C_SCL_BUF: R174.1, R176.2; also elsewhere on the board
BP_I2C_SDA: R177.2, U1.AA10 (IO_L9N_AD3N_44); also elsewhere on the board
EXP_IO33_0: U1.B15 (IO_L1P_AD11P_26); also elsewhere on the board
EXP_IO33_1: U1.A15 (IO_L1N_AD11N_26); also elsewhere on the board
EXP_IO33_3: U1.A14 (IO_L2N_AD10N_26); also elsewhere on the board
EXP_IO33_4: U1.B13 (IO_L3P_AD9P_26); also elsewhere on the board
EXP_IO33_5: U1.A13 (IO_L3N_AD9N_26); also elsewhere on the board
Fan1PWM: U1.AG10 (IO_L1P_AD11P_44); also elsewhere on the board
Fan1Tach: U1.AH10 (IO_L1N_AD11N_44); also elsewhere on the board
Fan2PWM: U1.AF11 (IO_L2P_AD10P_44); also elsewhere on the board
Fan2Tach: U1.AG11 (IO_L2N_AD10N_44); also elsewhere on the board
Fan3PWM: U1.AH11 (IO_L3N_AD9N_44); also elsewhere on the board
Fan3Tach: U1.AH12 (IO_L3P_AD9P_44); also elsewhere on the board
Fan4PWM: U1.AE10 (IO_L4P_AD8P_44); also elsewhere on the board
Fan4Tach: U1.AF10 (IO_L4N_AD8N_44); also elsewhere on the board
I2S_BCK: U1.W14 (IO_L9P_AD11P_24); also elsewhere on the board
I2S_DIN: U1.W13 (IO_L9N_AD11N_24); also elsewhere on the board
I2S_LRCK: U1.Y13 (IO_L10N_AD10N_24); also elsewhere on the board
LED_SPI_CS_BUF: R195.2, U1.AD14 (IO_L5N_HDGC_24); also elsewhere on the board
LED_SPI_MISO_BUF: R196.2, R197.1; also elsewhere on the board
LED_SPI_MOSI_BUF: R173.1; also elsewhere on the board
LED_SPI_SCK_BUF: R194.2, U1.AD15 (IO_L5P_HDGC_24); also elsewhere on the board
unnamed: R157.2, U1.F10 (IO_L5N_HDGC_25)
unnamed: R164.2, U1.D14 (IO_L5N_HDGC_AD7N_26)
unnamed: R141.2, U1.G11 (IO_L5P_HDGC_25)
unnamed: R148.2, U1.D15 (IO_L5P_HDGC_AD7P_26)
unnamed: R197.2, U1.AC13 (IO_L6N_HDGC_24)
unnamed: R155.2, U1.F11 (IO_L6N_HDGC_25)
unnamed: R163.2, U1.E13 (IO_L6N_HDGC_AD6N_26)
unnamed: R173.2, U1.AC14 (IO_L6P_HDGC_24)
unnamed: R139.2, U1.F12 (IO_L6P_HDGC_25)
unnamed: R147.2, U1.E14 (IO_L6P_HDGC_AD6P_26)
unnamed: R158.2, U1.D10 (IO_L7N_HDGC_25)
unnamed: R165.2, U1.F13 (IO_L7N_HDGC_AD5N_26)
unnamed: R142.2, U1.E10 (IO_L7P_HDGC_25)
unnamed: R149.2, U1.G13 (IO_L7P_HDGC_AD5P_26)
unnamed: R156.2, U1.D11 (IO_L8N_HDGC_25)
unnamed: R166.2, U1.E15 (IO_L8N_HDGC_AD4N_26)
unnamed: R140.2, U1.E12 (IO_L8P_HDGC_25)
unnamed: R150.2, U1.F15 (IO_L8P_HDGC_AD4P_26)
unnamed: R167.2, U1.G14 (IO_L9N_AD3N_26)
unnamed: R162.2, U1.B10 (IO_L9N_AD11N_25)
unnamed: R151.2, U1.G15 (IO_L9P_AD3P_26)
unnamed: R174.2, U1.AA11 (IO_L9P_AD3P_44)
unnamed: R146.2, U1.C11 (IO_L9P_AD11P_25)
unnamed: R168.2, U1.H13 (IO_L10N_AD2N_26)
unnamed: R172.2, U1.Y10 (IO_L10N_AD2N_44)
unnamed: R161.2, U1.A10 (IO_L10N_AD10N_25)
unnamed: R152.2, U1.H14 (IO_L10P_AD2P_26)
unnamed: R171.2, U1.W10 (IO_L10P_AD2P_44)
unnamed: R145.2, U1.B11 (IO_L10P_AD10P_25)
unnamed: R169.2, U1.J14 (IO_L11N_AD1N_26)
unnamed: R160.2, U1.A11 (IO_L11N_AD9N_25)
unnamed: R153.2, U1.K14 (IO_L11P_AD1P_26)
unnamed: R144.2, U1.A12 (IO_L11P_AD9P_25)
unnamed: R170.2, U1.L13 (IO_L12N_AD0N_26)
unnamed: R159.2, U1.C12 (IO_L12N_AD8N_25)
unnamed: R154.2, U1.L14 (IO_L12P_AD0P_26)
unnamed: R143.2, U1.D12 (IO_L12P_AD8P_25)
TDMA_CLK_BUF: R171.1; also elsewhere on the board
TDMA_SYNC_BUF: R172.1; also elsewhere on the board
UART_RX_BUF_0: R155.1, R178.2; also elsewhere on the board
UART_RX_BUF_1: R156.1, R179.2; also elsewhere on the board
UART_RX_BUF_2: R157.1, R180.2; also elsewhere on the board
UART_RX_BUF_3: R158.1, R181.2; also elsewhere on the board
UART_RX_BUF_4: R159.1, R182.2; also elsewhere on the board
UART_RX_BUF_5: R160.1, R183.2; also elsewhere on the board
UART_RX_BUF_6: R161.1, R184.2; also elsewhere on the board
UART_RX_BUF_7: R162.1, R185.2; also elsewhere on the board
UART_RX_BUF_8: R163.1, R193.2; also elsewhere on the board
UART_RX_BUF_9: R164.1, R192.2; also elsewhere on the board
UART_RX_BUF_10: R165.1, R191.2; also elsewhere on the board
UART_RX_BUF_11: R166.1, R190.2; also elsewhere on the board
UART_RX_BUF_12: R167.1, R189.2; also elsewhere on the board
UART_RX_BUF_13: R168.1, R188.2; also elsewhere on the board
UART_RX_BUF_14: R169.1, R187.2; also elsewhere on the board
UART_RX_BUF_15: R170.1, R186.2; also elsewhere on the board
UART_TX_BUF_0: R139.1; also elsewhere on the board
UART_TX_BUF_1: R140.1; also elsewhere on the board
UART_TX_BUF_2: R141.1; also elsewhere on the board
UART_TX_BUF_3: R142.1; also elsewhere on the board
UART_TX_BUF_4: R143.1; also elsewhere on the board
UART_TX_BUF_5: R144.1; also elsewhere on the board
UART_TX_BUF_6: R145.1; also elsewhere on the board
UART_TX_BUF_7: R146.1; also elsewhere on the board
UART_TX_BUF_8: R147.1; also elsewhere on the board
UART_TX_BUF_9: R148.1; also elsewhere on the board
UART_TX_BUF_10: R149.1; also elsewhere on the board
UART_TX_BUF_11: R150.1; also elsewhere on the board
UART_TX_BUF_12: R151.1; also elsewhere on the board
UART_TX_BUF_13: R152.1; also elsewhere on the board
UART_TX_BUF_14: R153.1; also elsewhere on the board
UART_TX_BUF_15: R154.1; also elsewhere on the board

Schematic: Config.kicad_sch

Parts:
U1: XCZU3EG-2SFVC784I; SFVC784_AMD; MPN XCZU3EG-2SFVC784I; LCSC C1550463

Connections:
GND: U1.P13 (GNDADC), U1.U7 (PUDC_B); also elsewhere on the board
